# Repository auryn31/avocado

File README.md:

# Avocado

A keyboard for Auryn

This is an ergogen based corne clone that I intend to modify and tweak as I descend into the rabbit hole

## Getting Started

```bash
git clone https://github.com/auryn31/avocado
cd avocado
yarn
```

## Ergogen

### Build

This will run Ergogen and build all of the output files.

```bash
npm run ergogen:build
```

### Watch

This will watch the `config.yaml` file and the `footprints` directory and run the build command whenever there are changes.

```bash
npm run ergogen:watch
```

## ZMK

The code will run by github actions and will be automatically generated their.
Just download the zip and push it onto your pro micro.

## Parts

- [Batteries 301230](https://de.aliexpress.com/item/1005007002754764.html)
- [Reset Switches](https://de.aliexpress.com/item/32873382894.html)
- [On/Off Switch](https://de.aliexpress.com/item/4000685483225.html)
- [Diodes](https://de.aliexpress.com/item/32849879904.html)
- [Sockets](https://de.aliexpress.com/item/4001122376295.html)
- [Battery Connector/Adapter/Pins](https://de.aliexpress.com/item/1005004955655144.html)
- [Nice!Nano Clone](https://de.aliexpress.com/item/1005006446457448.html)
- [DSA Keycaps](https://de.aliexpress.com/item/1005006005905021.html)
- [Akko Cream Blue](https://de.aliexpress.com/item/1005006382591392.html)

## Video on YouTube

[Part 1](https://youtu.be/ohu4tZ4qov8)
[Part 2](https://youtu.be/3RLsh07ZFMo)

## Thanks

- <a href="https://github.com/ergogen/ergogen" target="_blank">Ergogen</a>
- <a href="https://discord.gg/nbKcAZB" target="_blank">Absolem Club Discord</a>
- <a href="https://github.com/tsteffek/Ergogen-V4-Migration-Guide" target="_blank">V4 Migration Guide</a>
- <a href="https://gitlab.com/Audijo/keyboard" target="_blank">Claw</a>
- <a href="https://github.com/MrCarney/mrkeyboard" target="_blank">MrKeyboard</a>
- <a href="https://github.com/foostan/crkbd" target="_blank">Corne keyboard</a>
- <a href="https://github.com/zmkfirmware/zmk" target="_blank">ZMK</a>
- <a href="https://github.com/manna-harbour/miryoku_zmk" target="_blank">Miryoku ZMK</a>

## Local build

```sh
# One time setup
git clone https://github.com/zmkfirmware/zmk.git
npm install -g @devcontainers/cli

docker volume create --driver local -o o=bind -o type=none \\n  -o device="/Users/auryn/coding/avocado/config" zmk-config
docker volume create --driver local -o o=bind -o type=none \\n  -o device="/Users/auryn/coding/avocado/zephyr" zmk-modules
devcontainer up --workspace-folder "/Users/auryn/coding/zmk"

docker exec -w /workspaces/zmk -it a29e880249f3 /bin/bash

cd app
west update
west config build.cmake-args -- "-DSHIELD=avocado_left -DZMK_CONFIG=/workspaces/zmk-config"
west config build.cmake-args -- "-DSHIELD=avocado_right -DZMK_CONFIG=/workspaces/zmk-config"

# One or the other
west build -p -b nice_nano_v2 -- -DSHIELD=avocado_left
# west build -p -b seeeduino_xiao_ble -- -DSHIELD=avocado_left
```

## Resources

- goose keyboard: https://github.com/Pipshag/goosekb/blob/master/config/goose.keymap

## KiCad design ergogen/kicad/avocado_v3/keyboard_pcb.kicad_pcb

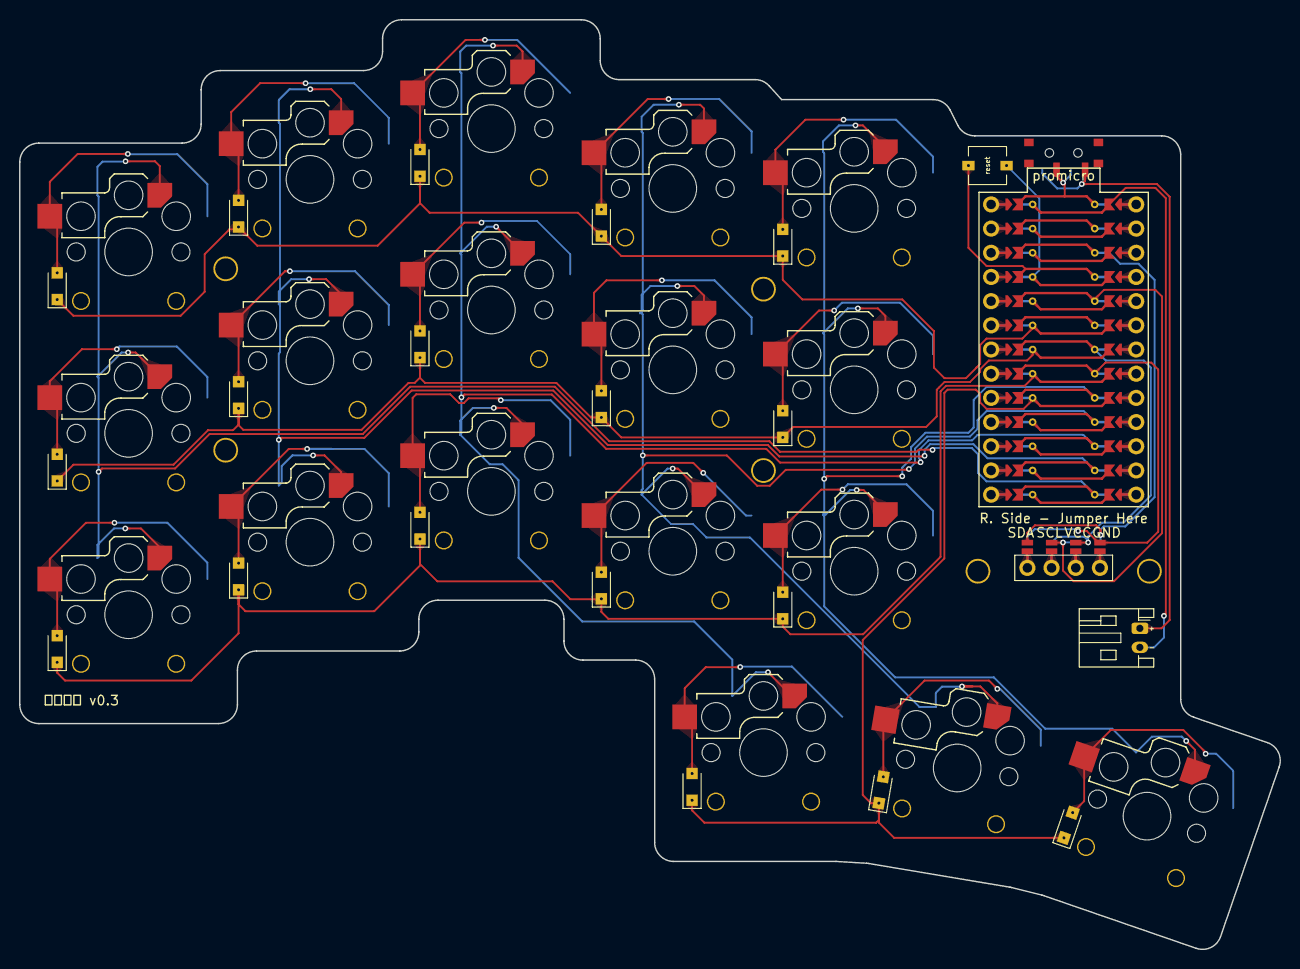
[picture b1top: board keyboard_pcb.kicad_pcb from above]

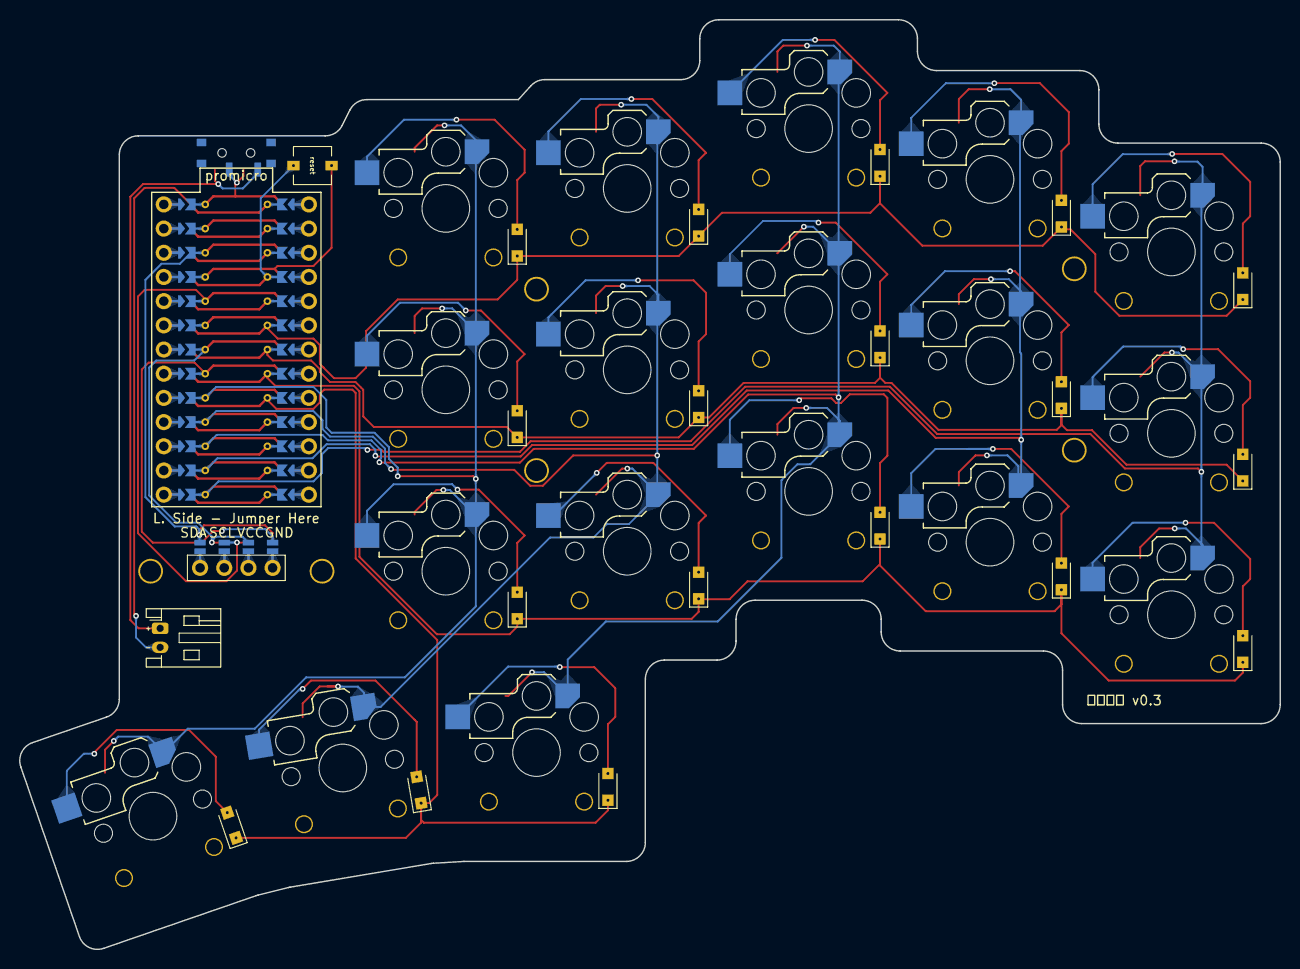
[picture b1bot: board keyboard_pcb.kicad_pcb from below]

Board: 2 copper layers, 132.4 x 97.6 mm, 46 parts (18 on the bottom side), 18 nets.

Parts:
D1, D2, D3, D4, D5, D6, D7, D8, D9, D10, D11, D12, D13, D14, D15, D16, D17, D18: Nexperia_CFP3_SOD-123W
DISP1: display_ssd1306
H1, H2, H3, H4, H5, H6: mounting_hole
S1, S2, S3, S4, S5, S6, S7, S8, S9, S10, S11, S12, S13, S14, S15, S16, S17, S18: switch_choc_v1_v2
S19: 434121025816
T1: SW_SPDT_PCM12
_2: JST_PH_S2B-PH-K_1x02_P2.00mm_Horizontal

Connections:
DISP1_1: DISP1.1, DISP1.10, DISP1.23
DISP1_2: DISP1.2, DISP1.11, DISP1.22
DISP1_3: DISP1.3, DISP1.12, DISP1.21
DISP1_4: DISP1.4, DISP1.13, DISP1.20
GND: DISP1.14, DISP1.24, S19.2
P2: D3.1, D3.2, D6.1, D6.2, D9.1, D9.2, D12.1, D12.2, D15.1, D15.2, S3.2, S6.2, S9.2, S12.2, S15.2
P3: D2.1, D2.2, D5.1, D5.2, D8.1, D8.2, D11.1, D11.2, D14.1, D14.2, S2.2, S5.2, S8.2, S11.2, S14.2
P4: D1.1, D1.2, D4.1, D4.2, D7.1, D7.2, D10.1, D10.2, D13.1, D13.2, S1.2, S4.2, S7.2, S10.2, S13.2
P5: D16.1, D16.2, D17.1, D17.2, D18.1, D18.2, S16.2, S17.2, S18.2
P10: S1.1, S2.1, S3.1
P14: S7.1, S8.1, S9.1, S16.1
P15: S10.1, S11.1, S12.1, S17.1
P16: S4.1, S5.1, S6.1
P18: S13.1, S14.1, S15.1, S18.1
P19: DISP1.17, DISP1.27
P20: DISP1.16, DISP1.26
VCC: DISP1.15, DISP1.25
pos: T1.1, _2.1

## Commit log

2024-07-11 my initial commit, wip
2024-07-12 update to add avocado image
2024-07-17 intermediate
    remove unused code/files
    add kicad files
    remove unused code
2024-07-17 add zmk build workflow
2024-07-17 update board root
2024-07-17 update path to build matrix
2024-07-17 update 2
2024-07-17 update 3
2024-07-17 remove /config
2024-07-17 remove unused files and move zephyr
2024-07-17 update config path
2024-07-17 rename board path
2024-07-17 modified west yaml
2024-07-17 test copy whole config
2024-07-17 trigger
2024-07-17 move level up to build
2024-07-17 update yaml to yml
2024-07-17 update import
2024-07-17 add my bastardkb keymapping
2024-07-17 remove unused files
2024-07-17 test, build worked before, but put in subdir now again
2024-07-17 last test with subdir
2024-07-17 Revert "last test with subdir"
    This reverts commit 128bed0b612757cd984eb55cfcdcc6ff3a9a3423.
2024-07-17 Revert "test, build worked before, but put in subdir now again"
    This reverts commit 75e9de483484be5255e85850c8ceb7b91f83410d.
2024-07-17 back to working state
2024-08-16 move thumbcluster more together and add all pins for pro micro clone
2024-08-25 update config
2024-08-28 update choc details
2024-09-09 add bt_clear
2024-09-09 update bt_clear
2024-09-16 update position of hole and battery connector
2024-09-28 add trackpoint config
2024-09-28 update layers
2024-09-28 change to petejohansons branch
2024-09-28 and again
2024-09-28 update compatible
2024-09-28 invert y direction and add press to select
2024-11-03 update pinpout
2024-11-03 update pinout again
2024-11-03 update pinout v3
2024-11-03 update config v4
2024-11-03 update config v5
2024-11-03 update config v6
2024-11-03 update config v7
2024-11-03 update config v8
2024-11-03 update config v9
2024-11-03 update config v10
2024-11-03 update invert
2024-11-03 update left
2024-11-04 update sensitivity
2024-11-04 update name of keyboard
2024-11-09 update trackpoint
2024-11-12 update name
2024-11-12 turn down sensitivity
2024-11-22 finalize choc keyboard
2024-12-22 add v3 / tofu
2024-12-22 update include
2024-12-22 Update keymap
2024-12-22 rename and update sda/sck
2024-12-22 config display
2024-12-22 typo
2024-12-22 try other pins
2024-12-22 add display?
2024-12-22 try with board build
2024-12-22 enable display
2024-12-22 update position of file
2024-12-22 update cnfig
2024-12-22 add i2c
2024-12-22 last try
2024-12-22 last last try
2024-12-22 try low bitrte
2024-12-22 make standard
2024-12-22 test
2024-12-22 add logging
2024-12-22 update log level
2024-12-22 test 2
2024-12-22 test 4
2024-12-22 update test 5
2024-12-22 reset to default?
2024-12-22 fix reset
2024-12-22 try again
2024-12-22 lost
2024-12-23 update conf
2024-12-23 remove board
2024-12-23 remove-board worked, update config not, lets see if this works
2024-12-23 update naming
2024-12-28 turn off sleep
2025-01-12 add case
2025-08-10 remove mouse parts
2025-08-17 add mount holes
2025-09-04 update to xiao gpio
2025-09-09 update shield
2025-09-20 enable rotary encoder
2025-09-20 try different config
2025-09-21 update trigger per rotation
2025-09-21 reduce steps
2025-09-21 add debugging
2025-09-21 update send values
2025-09-21 enable usb logging
2025-09-21 try adding encoder
2025-09-21 build again
2025-09-21 update again
2025-09-21 update to try pull up
2025-09-21 try just one encoder for testing
2025-09-21 move config
